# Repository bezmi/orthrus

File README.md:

# orthrus
56 key wireless split keyboard running on QMK. Staggered orthogonal layout

Refer to individual folders for help on the build, raise an issue if you need any extra help :)

To use with qmk, just merge the qmk_firmware/ directory in this repository with your downloaded qmk_firmware directory

# UPDATES

Over the time that I have been using this keyboard, the "sandwich" style battery holder has bee less than ideal. I have modified my keyboard with [these battery holders](https://au.rs-online.com/web/p/battery-holders-mounts/7188457/), which are epoxied to the top PCB for each half. The negative terminal of the battery holder is soldered to pad 3 "GND_P" on the top PCB with a short wire:

The positive terminal is soldered to the through-hole VCC connection with a short wire:

This is what it looks like now.

# Acknowledgements
Thanks to [@reversebias](https://github.com/reversebias) for the inspiration as well as the firmware to make this work and [@joric](https://github.com/joric) for making the firmware work with the cheaper nrf modules

Thanks to technomancy for the original 42 key [atreus](https://atreus.technomancy.us) design and profet for the [atreus62](http://shop.profetkeyboards.com/product/atreus62-keyboard) design that I have been using for quite a while.

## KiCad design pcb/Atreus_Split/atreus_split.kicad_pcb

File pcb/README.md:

# PCB

PCB design files and gerbers for the orthrus keyboard. See the [mitosis build log](https://imgur.com/a/mwTFj#JtzXTCD) for an overview of how to put this together.

There are a couple of minor differences. For example, for the programming header, my right angle connector footprint is too far in from the edge of the PCB, which resulted in the particular right angle headers I had not being reachable. I compromised by just using straight headers that go through the holes in the top (switch plate) pcb. It works just fine and the header is optional anyway. You could just as well solder temporary wires, program, then desolder before final assembly.

For the foam base, I did not have access to a lasercutter, so I cut a cloth mouse pad to size (including a cutout for the module on the bottom), cut all of the switch pins flush to the bottom of the PCB and hot glued the mousepad bits to the bottom. It is a little bumpy if you feel the bottom of the keyboard, but the typing feel is not compromised. Make sure you put tape on the module to avoid shorts!

For the receiver, I use the [mitosis receiver PCB](https://github.com/reversebias/mitosis-hardware). You can look at the BOM there (adjusting for extra switches, etc). I designed the PCBs to use the cheaper black nrf modules from aliexpress (Yj-14015), which are slightly smaller than the official waveshare module. For the receiver I had a legitimate waveshare module (blue) laying around, so I just used that, but soldering a Yj-14015 module to the receiver PCB can be very tricky. Feel free to extend the mitosis receiver pads and submit a pull request.

Make sure the PCB fab house can do 0.8mm slots. I've got mine manufactured from JLCPCB and the PCBs came out perfect.

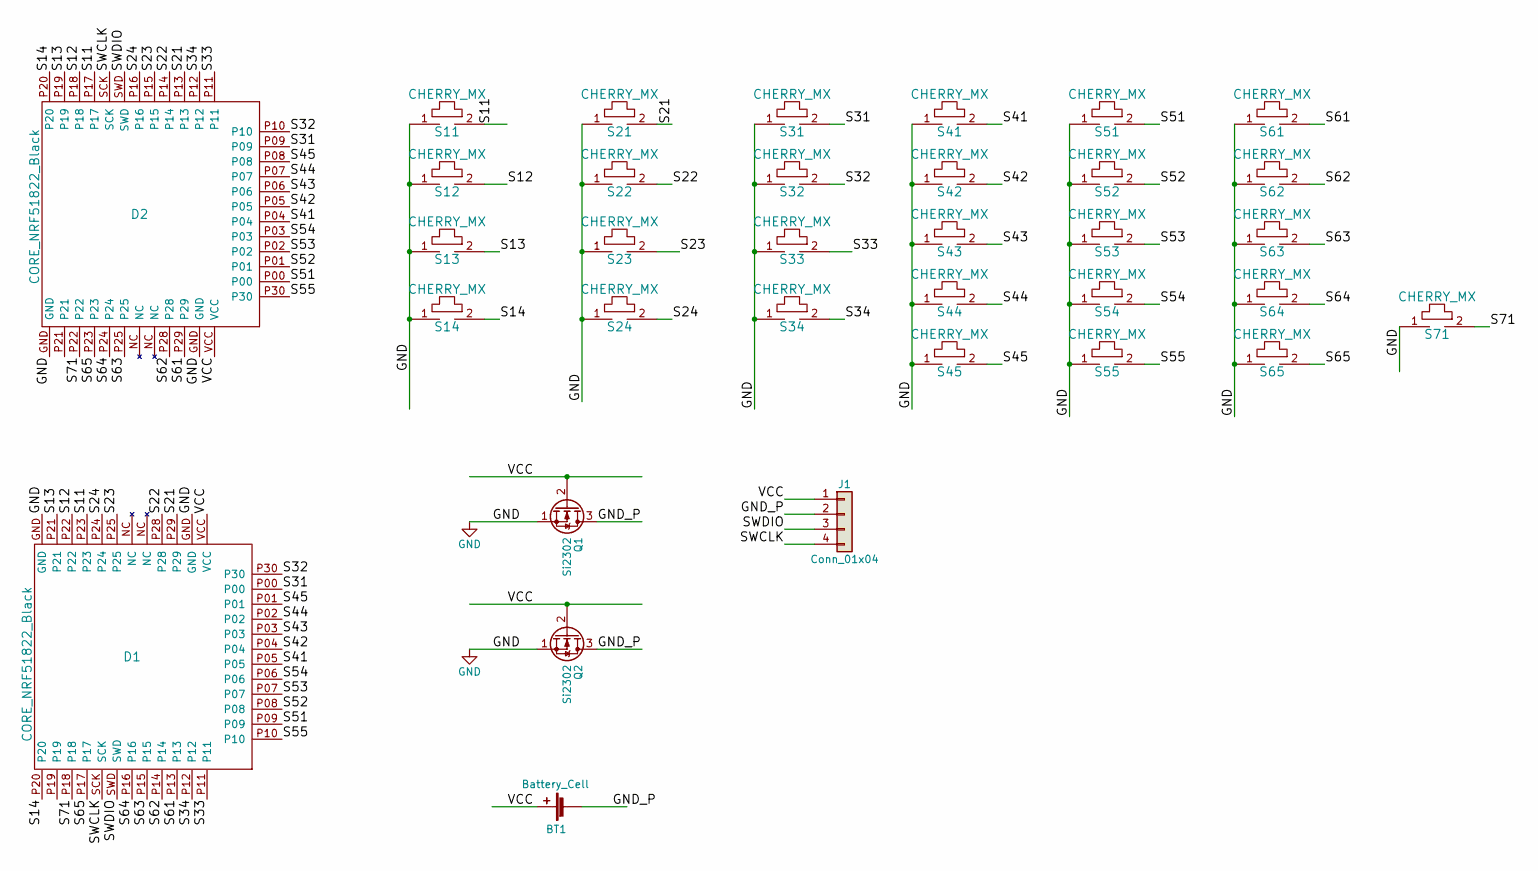
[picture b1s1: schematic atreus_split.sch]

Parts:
BT1: Battery_Cell; CR2032_pad
D1, D2: CORE_NRF51822_Black
J1: Conn_01x04; Pin_Header_Angled_1x04_Pitch2.54mm
Q1, Q2: Si2302; SI2302
S11, S12, S13, S14, S21, S22, S23, S24, S31, S32, S33, S34, S41, S42, S43, S44, S45, S51, S52, S53, S54, S55, S61, S62, S63, S64, S65, S71: CHERRY_MX; cherry

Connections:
/GND_P: BT1.2 (-), J1.2, Q1.3 (D), Q2.3 (D)
/S11: D1.P23, D2.P17, S11.2
/S12: D1.P22, D2.P18, S12.2
/S13: D1.P21, D2.P19, S13.2
/S14: D1.P20, D2.P20, S14.2
/S21: D1.P29, D2.P13, S21.2
/S22: D1.P28, D2.P14, S22.2
/S23: D1.P25, D2.P15, S23.2
/S24: D1.P24, D2.P16, S24.2
/S31: D1.P00, D2.P09, S31.2
/S32: D1.P30, D2.P10, S32.2
/S33: D1.P11, D2.P11, S33.2
/S34: D1.P12, D2.P12, S34.2
/S41: D1.P05, D2.P04, S41.2
/S42: D1.P04, D2.P05, S42.2
/S43: D1.P03, D2.P06, S43.2
/S44: D1.P02, D2.P07, S44.2
/S45: D1.P01, D2.P08, S45.2
/S51: D1.P09, D2.P00, S51.2
/S52: D1.P08, D2.P01, S52.2
/S53: D1.P07, D2.P02, S53.2
/S54: D1.P06, D2.P03, S54.2
/S55: D1.P10, D2.P30, S55.2
/S61: D1.P13, D2.P29, S61.2
/S62: D1.P14, D2.P28, S62.2
/S63: D1.P15, D2.P25, S63.2
/S64: D1.P16, D2.P24, S64.2
/S65: D1.P17, D2.P23, S65.2
/S71: D1.P18, D2.P22, S71.2
/SWCLK: D1.SCK, D2.SCK, J1.4
/SWDIO: D1.SWD, D2.SWD, J1.3
/VCC: BT1.1 (+), D1.VCC, D2.VCC, J1.1, Q1.2 (G), Q2.2 (G)
GND: D1.GND, D2.GND, Q1.1 (S), Q2.1 (S), S11.1, S12.1, S13.1, S14.1, S21.1, S22.1, S23.1, S24.1, S31.1, S32.1, S33.1, S34.1, S41.1, S42.1, S43.1, S44.1, S45.1, S51.1, S52.1, S53.1, S54.1, S55.1, S61.1, S62.1, S63.1, S64.1, S65.1, S71.1

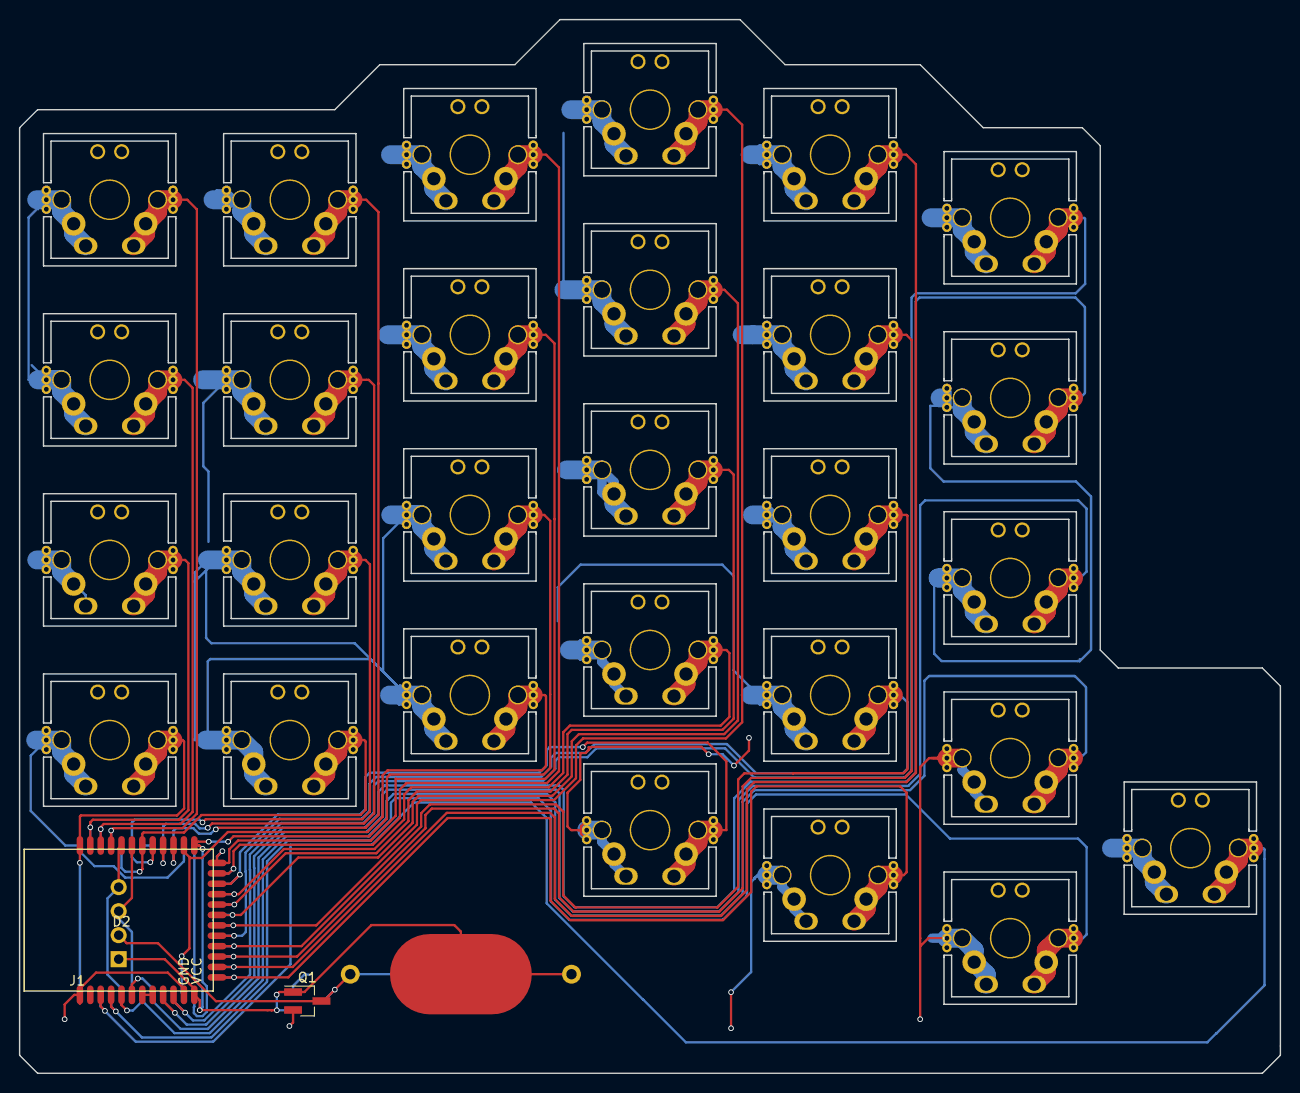
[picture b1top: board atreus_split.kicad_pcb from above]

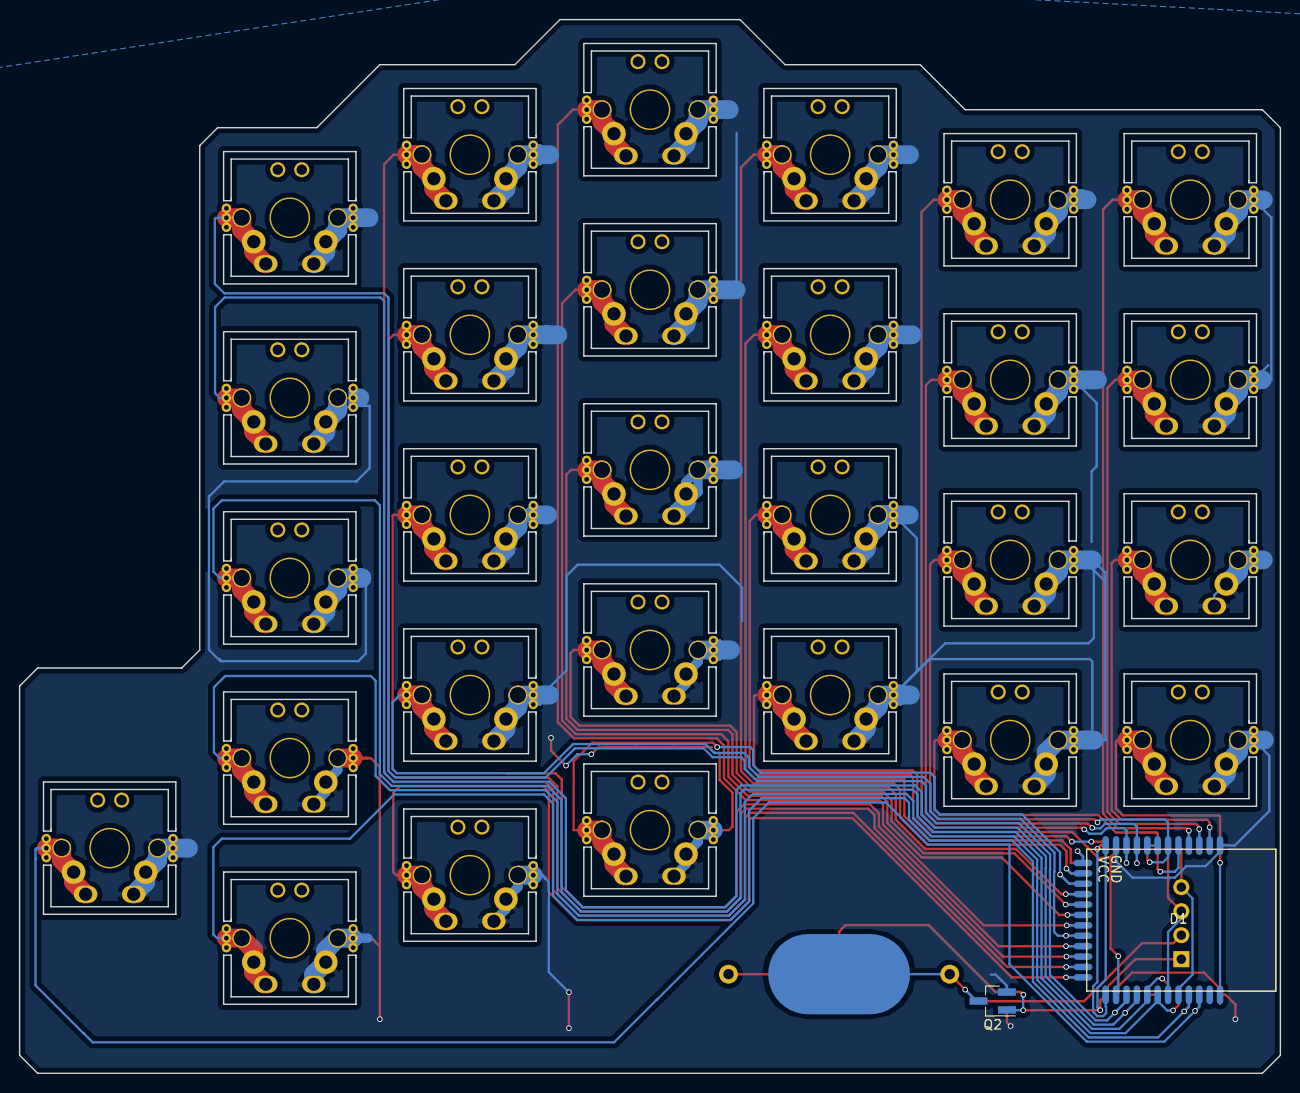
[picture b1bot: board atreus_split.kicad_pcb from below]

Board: 2 copper layers, 133.4 x 111.4 mm, 34 parts (2 on the bottom side), 33 nets.

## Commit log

2018-06-26 moved gerbers folder
2018-06-26 added acknowledgements
2018-06-26 acknowledged technomancy and profet
2019-08-12 added update on battery holders
2019-08-12 fixed images
